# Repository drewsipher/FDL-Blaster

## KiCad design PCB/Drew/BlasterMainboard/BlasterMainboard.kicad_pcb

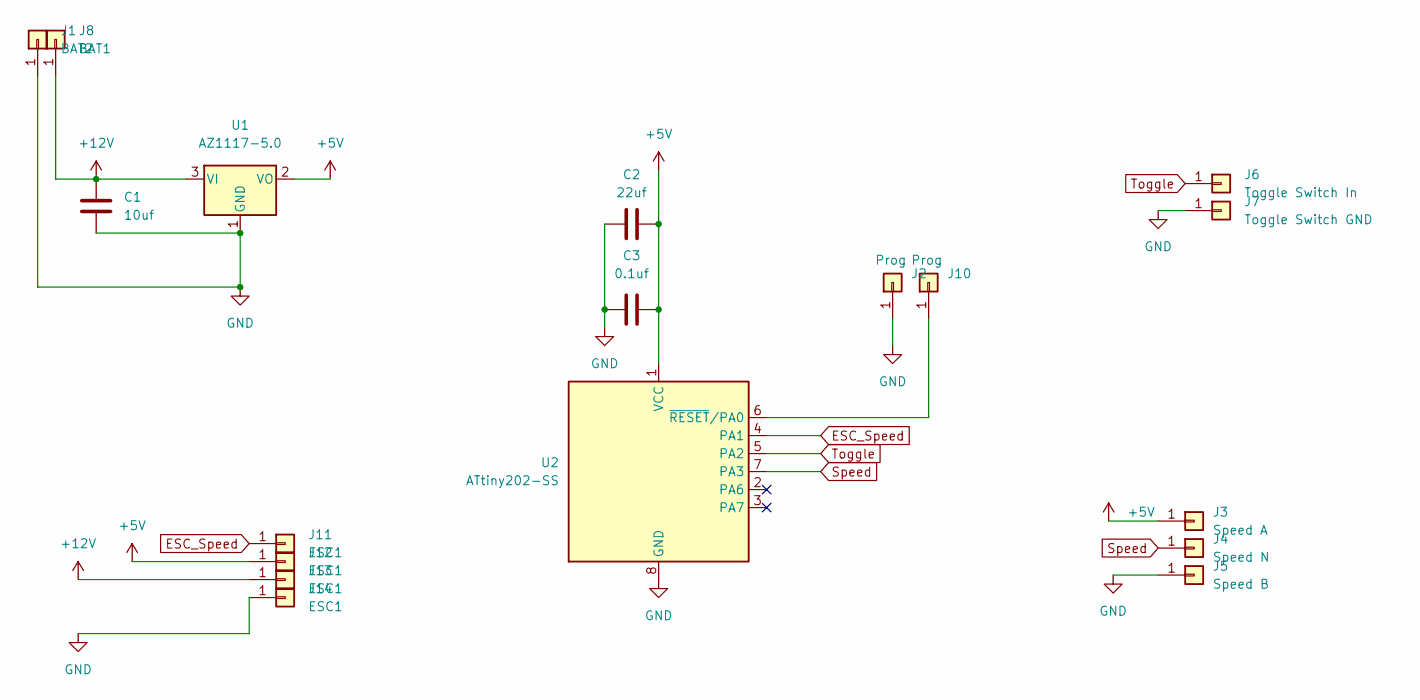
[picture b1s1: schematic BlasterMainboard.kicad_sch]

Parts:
C1: 10uf; C_1206_3216Metric
C2: 22uf; C_1206_3216Metric
C3: 0.1uf; C_0805_2012Metric
J1: BAT2; TestPoint_Keystone_5015_Micro-Minature
J2, J10: Prog; TestPoint_Pad_1.5x1.5mm
J3: Speed A; TestPoint_Keystone_5015_Micro-Minature
J4: Speed N; TestPoint_Keystone_5015_Micro-Minature
J5: Speed B; TestPoint_Keystone_5015_Micro-Minature
J6: Toggle Switch In; TestPoint_Keystone_5015_Micro-Minature
J7: Toggle Switch GND; TestPoint_Keystone_5015_Micro-Minature
J8: BAT1; TestPoint_Keystone_5015_Micro-Minature
J11, J12, J13, J14: ESC1; TestPoint_Pad_1.5x1.5mm
U1: AZ1117-5.0; SOT-223
U2: ATtiny202-SS; SOIC-8_3.9x4.9mm_P1.27mm

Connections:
+5V: C2.1, C3.1, J3.1, J12.1, U1.2 (VO), U2.1 (VCC)
+12V: C1.1, J8.1, J13.1, U1.3 (VI)
ESC_Speed: J11.1, U2.4 (PA1)
GND: C1.2, C2.2, C3.2, J1.1, J2.1, J5.1, J7.1, J14.1, U1.1 (GND), U1.4, U2.8 (GND)
unnamed: J10.1, U2.6 (~RESET/PA0)
Speed: J4.1, U2.7 (PA3)
Toggle: J6.1, U2.5 (PA2)

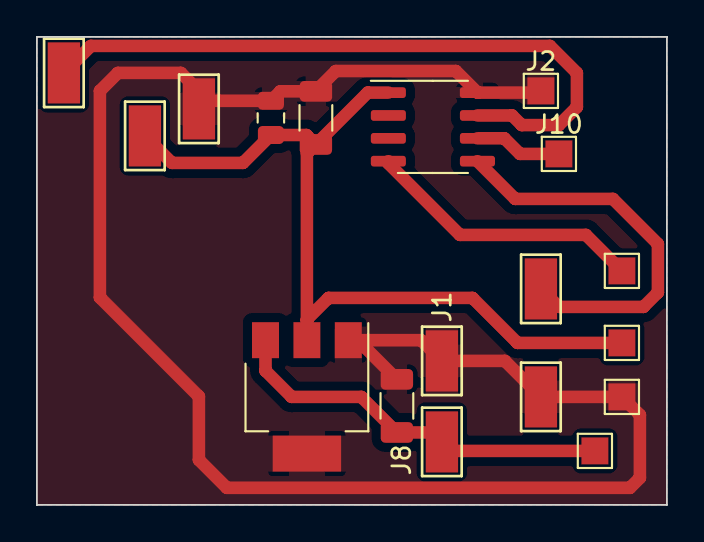
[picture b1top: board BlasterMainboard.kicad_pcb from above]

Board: 2 copper layers, 35.0 x 26.0 mm, 18 parts (0 on the bottom side), 7 nets.

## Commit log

2023-04-14 Modded Brushless mounts
2023-04-15 Switched to Attiny85
